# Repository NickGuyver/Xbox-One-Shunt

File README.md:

---

# Xbox One Bliss Hack Efuse Side-Channel Current Monitor (INA181 + TLV3201)

# *THIS IS COMPLETELY UNTESTED AND WAS CREATED WITH LOADS OF HELP USE AS A REFERENCE ONLY*

## Hardware

### Schematic

### PCB Layout

### PCB Render

This project implements a small analog front-end designed to detect short current spikes on a low-voltage rail and convert them into a clean digital timing signal suitable for capture by a microcontroller.

The circuit measures current through a shunt resistor, amplifies the resulting voltage drop, and feeds the signal into a high-speed comparator that generates a logic pulse.

The digital output can be captured by a microcontroller (for example a **Teensy**) for precise timing measurements.

---

# How It Works

## 1. Current Sensing

A low-value shunt resistor is placed in series with the monitored rail.

```
Rshunt ≈ 0.5 Ω
```

Current spikes create a small differential voltage:

```
Vshunt = I × Rshunt
```

Typical observed range:

```
0–100 mV
```

---

## 2. Signal Amplification

An **INA181A1 current sense amplifier** measures the voltage across the shunt and amplifies it.

Gain:

```
20 V/V
```

Example amplified output:

| Shunt Voltage | Amplified Output |
| ------------- | ---------------- |
| 25 mV         | 0.5 V            |
| 50 mV         | 1.0 V            |
| 75 mV         | 1.5 V            |
| 100 mV        | 2.0 V            |

Amplifier output net:

```
AMP_OUT
```

---

## 3. Threshold Detection

The amplified signal is fed into a **TLV3201 high-speed comparator**.

```
IN+  → AMP_OUT
IN−  → VREF
```

A resistor divider generates the threshold voltage:

```
VREF ≈ 1.5 V
```

When the amplified signal exceeds this threshold, the comparator outputs a digital signal.

Output net:

```
CMP_OUT
```

---

## 4. Comparator Hysteresis

A feedback resistor introduces small hysteresis to prevent noise from causing repeated triggers.

```
CMP_OUT → 1MΩ → VREF
```

This stabilizes switching while maintaining high timing accuracy.

## Voltage Levels and Threshold Behavior

Two different voltages exist in this circuit:

1. **Rail voltage** being monitored  
2. **Small differential voltage across the shunt resistor**

Typical operating conditions:

- Rail baseline: **0.9–1.0 V**
- Shunt signal: **0–100 mV**
- Amplifier: **INA181A1 (20 V/V gain)**
- Comparator supply: **3.3 V**

---

### Differential Measurement

The INA181 measures only the **voltage difference across the shunt**:

Vshunt = SHUNT_H − SHUNT_L

The rail voltage itself is the **common-mode level**, while the shunt voltage is the signal being amplified.

---

### Amplifier Output

With the INA181A1:

Vout = 20 × Vshunt

Example outputs:

| Vshunt | AMP_OUT |
|------:|--------:|
| 25 mV | 0.5 V |
| 50 mV | 1.0 V |
| 75 mV | 1.5 V |
| 100 mV | 2.0 V |

---

### Comparator Threshold

A resistor divider generates the reference voltage:

3.3V --- R1 --- VREF --- R2 --- GND

VREF = 3.3 × (R2 / (R1 + R2))

With:

- **R1 = 12 kΩ**
- **R2 = 10 kΩ**

VREF ≈ 1.5 V

---

### Equivalent Shunt Threshold

Because the amplifier gain is **20×**, the comparator threshold corresponds to:

Vshunt_threshold = VREF / 20

Vshunt_threshold ≈ 75 mV

---

### Summary

With the current component values:

- **INA181A1 gain:** 20×  
- **Comparator threshold:** ~1.5 V  
- **Shunt trigger level:** ~75 mV  

The rail voltage (~0.9 V) acts only as the **common-mode input**, while switching behavior depends on the **differential shunt signal**.

---

# Signal Chain

```
Current spike
   │
   ▼
Shunt resistor (0.5Ω)
   │
   ▼
INA181 current sense amplifier
   │
   ▼
Amplified analog signal (AMP_OUT)
   │
   ▼
TLV3201 comparator
   │
   ▼
Digital pulse (CMP_OUT)
   │
   ▼
Microcontroller timing capture
```

---

# Hardware Notes

* Supply voltage: **3.3 V**
* Amplifier gain: **20 V/V**
* Shunt resistor: **0.5 Ω**
* Comparator hysteresis resistor: **1 MΩ**
* Decoupling capacitors: **100 nF**

### Layout Guidelines

* Place the **INA181 close to the shunt resistor**
* Use **short differential traces** for the shunt sense inputs
* Keep comparator input traces short

---

---

# Credits

The PCB layout was created by another contributor.

This repository contains the schematic, design files, and documentation for the circuit.

---

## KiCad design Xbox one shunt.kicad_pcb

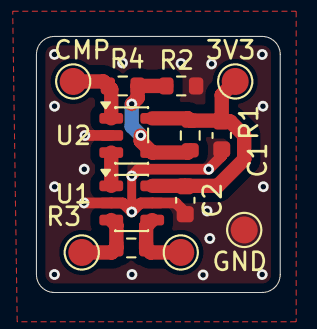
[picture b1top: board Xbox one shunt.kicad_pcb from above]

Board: 2 copper layers, 13.5 x 14.2 mm, 13 parts (0 on the bottom side), 7 nets.

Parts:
3V3: TestPoint; TestPoint_Pad_D1.5mm
C1, C2: 100nF; C_0603_1608Metric
CMP: TestPoint; TestPoint_Pad_D1.5mm
GND: TestPoint; TestPoint_Pad_D1.5mm
R1: 12kΩ; R_0603_1608Metric
R2: 10KΩ; R_0603_1608Metric
R3: R_Shunt 0.5Ω; R_0603_1608Metric
R4: 1MΩ; R_0603_1608Metric
TP2, TP3: TestPoint; TestPoint_Pad_D1.5mm
U1: INA181A1-Q1; SOT-23-6
U2: TLV3201AIDCKR; SOT-23-5

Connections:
+3.3V: 3V3.1, C1.2, C2.2, R1.1, U1.6 (V+), U2.5 (VCC)
/AMP_OUT: U1.1, U2.3 (IN+)
/CMP_OUT: CMP.1, R4.2, U2.1 (OUT)
/SHUNT_H: R3.1, TP2.1, U1.3 (+)
/SHUNT_L: R3.2, TP3.1, U1.4 (-)
/VREF: R1.2, R2.1, R4.1, U2.4 (IN-)
GND: C1.1, C2.1, GND.1, R2.2, U1.2 (GND), U1.5 (REF), U2.2 (GND)

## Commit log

2026-03-16 fixed images
2026-03-16 Fix image source paths in README.md
2026-03-16 Add disclaimer to README about untested status
    Added a disclaimer about the project being untested.
2026-03-16 More fixes on the pcb
2026-03-16 Update .gitignore to include additional file types
2026-03-16 Add .zip files to .gitignore
2026-03-16 quick fixes
